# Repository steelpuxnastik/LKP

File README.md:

# LKP

レンくんピアノ (Len-kun Piano)

Capacitive touch slider controller for rhythm games.

# Contents

## pcb/LKP-Core

Microcontroller board for use with LKP electrode boards. Supports up to 32 channel of self capacitance input. Includes a WS281x LED driver channel with protection resistor. Supports I2C or UART as communication methods.

For sample firmware for use with LKP-Core, see [LKP-FW](https://github.com/Project-Alpaca/LKP-FW).

Requires KiCad version 5.99 (nightly) (supports `kicad_pcb format >= 20210816`).

### Pin mapping

I/O port:

| \#  | Description |
| --- | ----------- |
|  1  | GND |
|  2  | INT |
|  3  | SCL/RX |
|  4  | SDA/TX |
|  5  | GND |
|  6  | +5V |

WS281x LED connector:

| \#  | Description |
| --- | ----------- |
|  1  | GND |
|  2  | LED |

SWD connector:

| \#  | Description |
| --- | ----------- |
|  1  | VTARG |
|  2  | GND |
|  3  | RESET |
|  4  | SWCLK |
|  5  | SWDIO |

## pcb/LKP-Diva-Electrode-Tile

Electrode board for Project DIVA Future Tone slider controller. Works as a 2-tile setup. Both tiles use the same design, with right tile being a 180 degree rotated version of the left tile.

Requires KiCad version 5.99 (nightly) (supports `kicad_pcb format >= 20210228`) for hatched fills.

# BOM

## LKP-Core

- **C1, C4, C6, C10**: Generic 1uF 0603 X5R ceramic capacitor. (I used `CC0603KRX5R8BB105`)
- **C2, C3, C5, C8, C11**: Generic 100nF 0603 ceramic capacitor. (I used `CL10B104KA8NNNC`)
- **C7**: `GRM2195C1H103JA01D`.
- **C9**: `GRM21B5C2J222FWAAL`.
- **C12**: Generic 10uF EIA-3216-18 tantalum capacitor.
- **D1**: Generic SOD-123 Schottky diode (`MBR0520L`).
- **D2**: Generic 0805 LED (yellow color).
- **FB1**: Generic 1206 ferrite bead (330ohm@100MHz).
- **J1, J2**: Straight female .1" header 2x9.
- **J3**: JST XH 2 positions.
- **J4**: Straight male .1" header 1x6.
- **J5**: Straight male .1" header 1x5.
- **J6**: **Angled** male .1" header 1x2 or JST XH 2 positions
- **R1**: Generic 1kohm 5% 0603 resistor.
- **R2**: Generic 470ohm 5% 0603 resistor.
- **R3, R4**: Generic 560ohm 5% 0603 resistor.
- **RN\***: Generic 560ohm 5% 0402x4 convex resistor array (I used `4D02WGJ0561TCE`).
- **U1**: `CY8C4246AZI-M445` (or `CY8C4247AZI-M485`, Needs minor firmware modifications).

## LKP-Diva-Electrode-Tile

- **J1**: Straight male .1" SMD header 2x9 (**without** bumps at the bottom).
  - This can be hard to find. For small scale DIY manufacturing try searching "pin header double smd" on aliexpress.

# Powering

By default LKP expects 5V power. Using lower supply voltage down to 1.8V is possible by modifying the power specs in LKP-FW and adding a level shifter module to the WS281x driver pin (labeled as LED on board). Reference voltage for I/O can be approximated by tapping into the VTARG pin on the SWD port.

# Known issues / Erratas

- (LKP-Core v1.0) The reverse voltage protection diode (D1) does not protect C12. Proceed with caution when connecting the power to make sure the polarity is correct.
- (LKP-Core v1.1) When used with LKP-Assy, connector J4, J5 and J6 may collide with the bottom of LKP-Assy. A workaround would be soldering all the specified connectors on the back side of the PCB instead. Also, when using LKP-IF-Qwiic, J4 and J5 must be soldered on the back side.
- (LKP-Core v1.2b) Changes of some parts that I have and I want to use: J1, J2 to JST XH, J4 from 4 to 6 pin, C9 to 0805 size, FB1 to 1206 size and changes in silkscreen. 

[qwiic]: https://www.sparkfun.com/qwiic
[stemmaqt]: https://learn.adafruit.com/introducing-adafruit-stemma-qt/what-is-stemma-qt

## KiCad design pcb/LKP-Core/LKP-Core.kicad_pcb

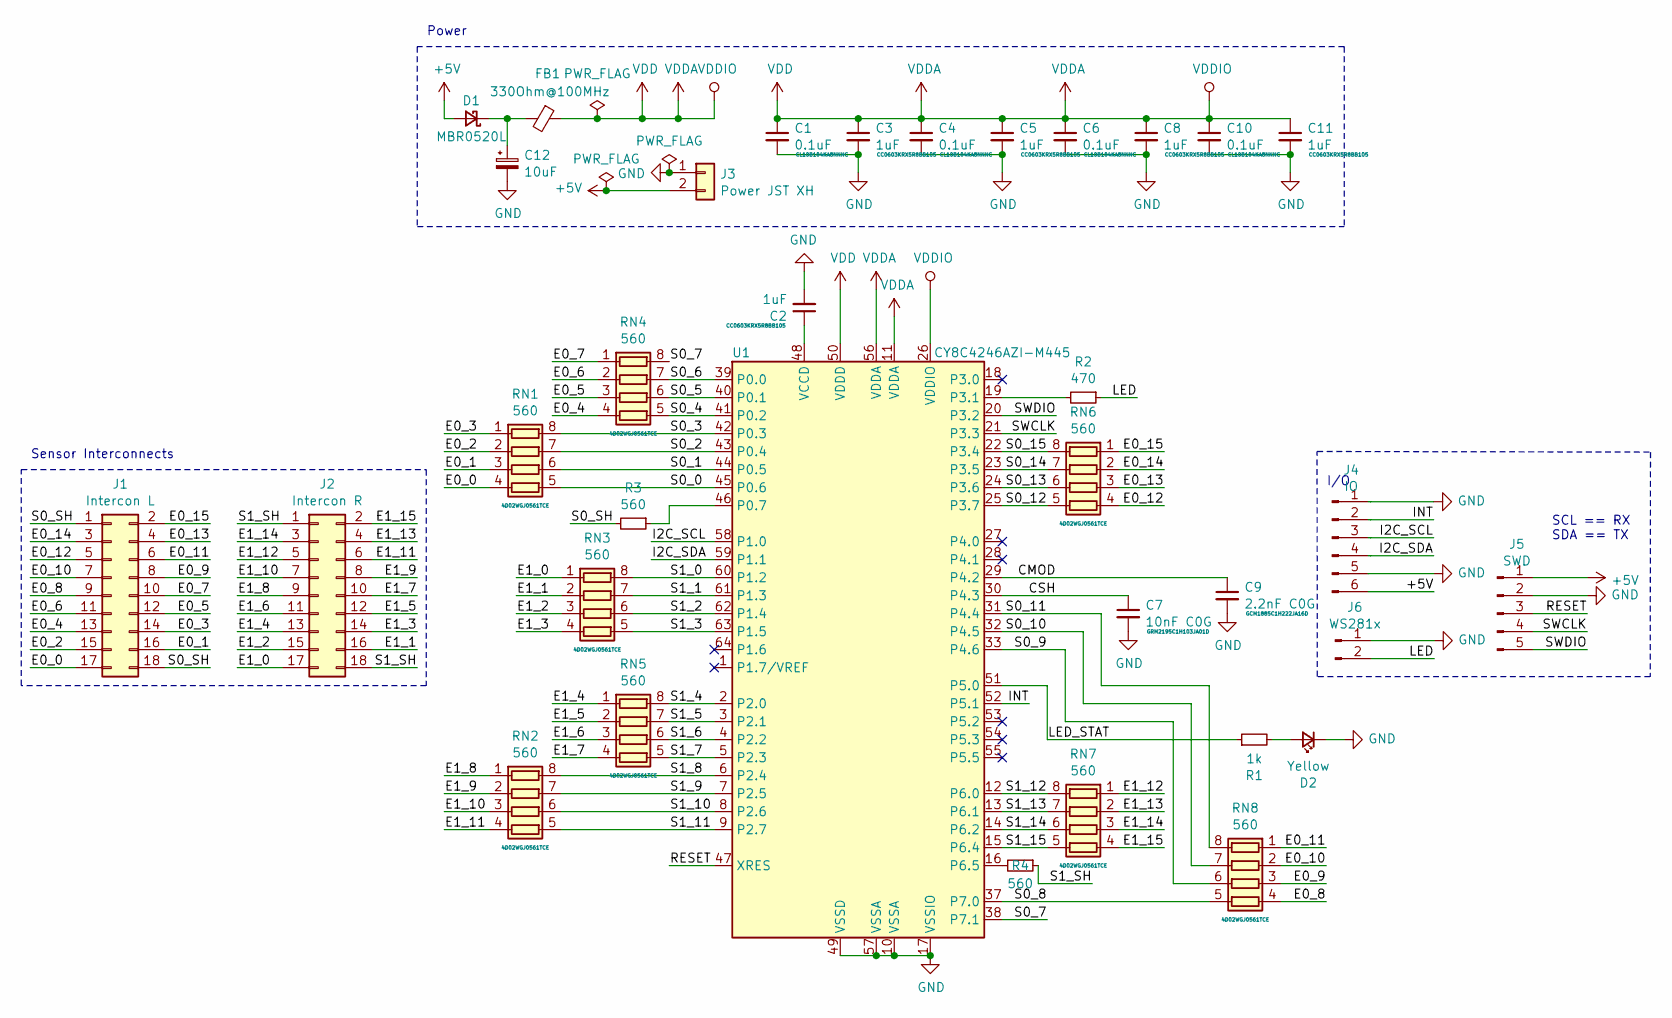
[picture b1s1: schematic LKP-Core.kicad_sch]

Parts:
C1, C4, C6, C10: 0.1uF; C_0603_1608Metric; Part Number CL10B104KA8NNNC
C2, C3, C5, C8, C11: 1uF; C_0603_1608Metric; Part Number CC0603KRX5R8BB105
C7: 10nF C0G; C_0805_2012Metric; Part Number GRM2195C1H103JA01D
C9: 2.2nF C0G; C_0805_2012Metric; Part Number GCM1885C1H222JA16D
C12: 10uF; CP_EIA-3216-18_Kemet-A
D1: MBR0520L; D_SOD-123; Part Number MBR0520L
D2: Yellow; LED_0805_2012Metric_Castellated
FB1: 330Ohm@100MHz; L_1206_3216Metric
J1: Intercon L; PinSocket_2x09_P2.54mm_Vertical
J2: Intercon R; PinSocket_2x09_P2.54mm_Vertical
J3: Power JST XH; JST_XH_B2B-XH-A_1x02_P2.50mm_Vertical
J4: IO; PinHeader_1x06_P2.54mm_Vertical
J5: SWD; PinHeader_1x05_P2.54mm_Vertical
J6: WS281x; JST_XH_B2B-XH-A_1x02_P2.50mm_Vertical
R1: 1k; R_0603_1608Metric
R2: 470; R_0603_1608Metric
R3, R4: 560; R_0603_1608Metric
RN1, RN2, RN3, RN4, RN5, RN6, RN7, RN8: 560; R_Array_Convex_4x0402; Part Number 4D02WGJ0561TCE
U1: CY8C4246AZI-M445; TQFP-64_10x10mm_P0.5mm; Part Number CY8C4246AZI-M445

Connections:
+5V: D1.2 (A), J3.2, J4.6, J5.1
/CMOD: C9.1, U1.29 (P4.2)
/CSH: C7.1, U1.30 (P4.3)
/E0_0: J1.17, RN1.4 (R4.1)
/E0_1: J1.16, RN1.3 (R3.1)
/E0_2: J1.15, RN1.2 (R2.1)
/E0_3: J1.14, RN1.1 (R1.1)
/E0_4: J1.13, RN4.4 (R4.1)
/E0_5: J1.12, RN4.3 (R3.1)
/E0_6: J1.11, RN4.2 (R2.1)
/E0_7: J1.10, RN4.1 (R1.1)
/E0_8: J1.9, RN8.4 (R4.1)
/E0_9: J1.8, RN8.3 (R3.1)
/E0_10: J1.7, RN8.2 (R2.1)
/E0_11: J1.6, RN8.1 (R1.1)
/E0_12: J1.5, RN6.4 (R4.1)
/E0_13: J1.4, RN6.3 (R3.1)
/E0_14: J1.3, RN6.2 (R2.1)
/E0_15: J1.2, RN6.1 (R1.1)
/E1_0: J2.17, RN3.1 (R1.1)
/E1_1: J2.16, RN3.2 (R2.1)
/E1_2: J2.15, RN3.3 (R3.1)
/E1_3: J2.14, RN3.4 (R4.1)
/E1_4: J2.13, RN5.1 (R1.1)
/E1_5: J2.12, RN5.2 (R2.1)
/E1_6: J2.11, RN5.3 (R3.1)
/E1_7: J2.10, RN5.4 (R4.1)
/E1_8: J2.9, RN2.1 (R1.1)
/E1_9: J2.8, RN2.2 (R2.1)
/E1_10: J2.7, RN2.3 (R3.1)
/E1_11: J2.6, RN2.4 (R4.1)
/E1_12: J2.5, RN7.1 (R1.1)
/E1_13: J2.4, RN7.2 (R2.1)
/E1_14: J2.3, RN7.3 (R3.1)
/E1_15: J2.2, RN7.4 (R4.1)
/I2C_SCL: J4.3, U1.58 (P1.0)
/I2C_SDA: J4.4, U1.59 (P1.1)
/INT: J4.2, U1.52 (P5.1)
/LED: J6.2, R2.1
/LED_STAT: R1.1, U1.51 (P5.0)
/RESET: J5.3, U1.47 (XRES)
/S0_0: RN1.5 (R4.2), U1.45 (P0.6)
/S0_1: RN1.6 (R3.2), U1.44 (P0.5)
/S0_2: RN1.7 (R2.2), U1.43 (P0.4)
/S0_3: RN1.8 (R1.2), U1.42 (P0.3)
/S0_4: RN4.5 (R4.2), U1.41 (P0.2)
/S0_5: RN4.6 (R3.2), U1.40 (P0.1)
/S0_6: RN4.7 (R2.2), U1.39 (P0.0)
/S0_7: RN4.8 (R1.2), U1.38 (P7.1)
/S0_8: RN8.5 (R4.2), U1.37 (P7.0)
/S0_9: RN8.6 (R3.2), U1.33 (P4.6)
/S0_10: RN8.7 (R2.2), U1.32 (P4.5)
/S0_11: RN8.8 (R1.2), U1.31 (P4.4)
/S0_12: RN6.5 (R4.2), U1.25 (P3.7)
/S0_13: RN6.6 (R3.2), U1.24 (P3.6)
/S0_14: RN6.7 (R2.2), U1.23 (P3.5)
/S0_15: RN6.8 (R1.2), U1.22 (P3.4)
/S0_SH: J1.1, J1.18, R3.2
/S1_0: RN3.8 (R1.2), U1.60 (P1.2)
/S1_1: RN3.7 (R2.2), U1.61 (P1.3)
/S1_2: RN3.6 (R3.2), U1.62 (P1.4)
/S1_3: RN3.5 (R4.2), U1.63 (P1.5)
/S1_4: RN5.8 (R1.2), U1.2 (P2.0)
/S1_5: RN5.7 (R2.2), U1.3 (P2.1)
/S1_6: RN5.6 (R3.2), U1.4 (P2.2)
/S1_7: RN5.5 (R4.2), U1.5 (P2.3)
/S1_8: RN2.8 (R1.2), U1.6 (P2.4)
/S1_9: RN2.7 (R2.2), U1.7 (P2.5)
/S1_10: RN2.6 (R3.2), U1.8 (P2.6)
/S1_11: RN2.5 (R4.2), U1.9 (P2.7)
/S1_12: RN7.8 (R1.2), U1.12 (P6.0)
/S1_13: RN7.7 (R2.2), U1.13 (P6.1)
/S1_14: RN7.6 (R3.2), U1.14 (P6.2)
/S1_15: RN7.5 (R4.2), U1.15 (P6.4)
/S1_SH: J2.1, J2.18, R4.1
/SWCLK: J5.4, U1.21 (P3.3)
/SWDIO: J5.5, U1.20 (P3.2)
GND: C1.2, C2.2, C3.2, C4.2, C5.2, C6.2, C7.2, C8.2, C9.2, C10.2, C11.2, C12.2, D2.1 (K), J3.1, J4.1, J4.5, J5.2, J6.1, U1.10 (VSSA), U1.17 (VSSIO), U1.49 (VSSD), U1.57 (VSSA)
unnamed: C2.1, U1.48 (VCCD)
unnamed: C12.1, D1.1 (K), FB1.2
unnamed: D2.2 (A), R1.2
unnamed: R2.2, U1.19 (P3.1)
unnamed: R3.1, U1.46 (P0.7)
unnamed: R4.2, U1.16 (P6.5)
VDD: C1.1, C3.1, C4.1, C5.1, C6.1, C8.1, C10.1, C11.1, FB1.1, U1.11 (VDDA), U1.26 (VDDIO), U1.50 (VDDD), U1.56 (VDDA)

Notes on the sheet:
Sensor Interconnects
Power
I/O
SCL == RX SDA == TX

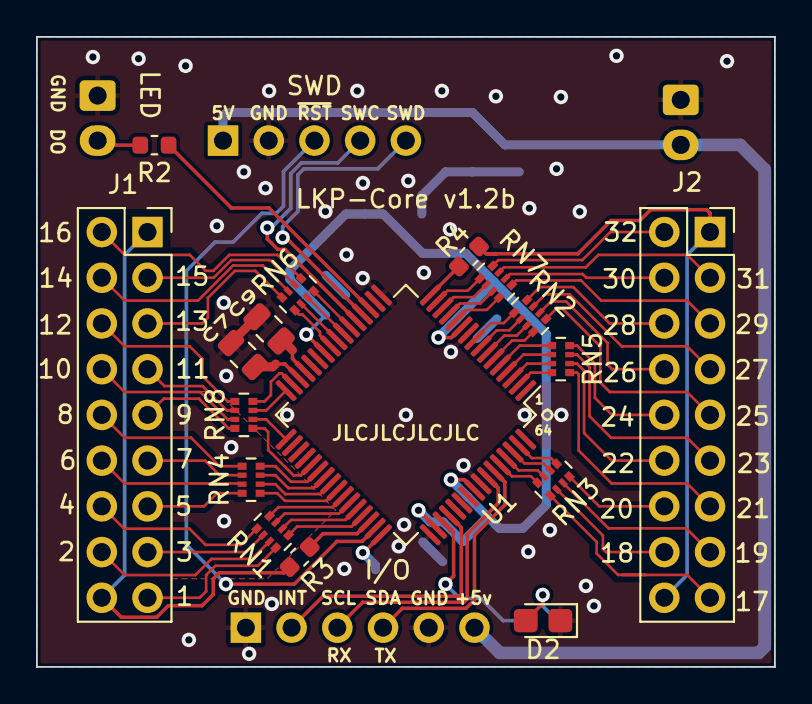
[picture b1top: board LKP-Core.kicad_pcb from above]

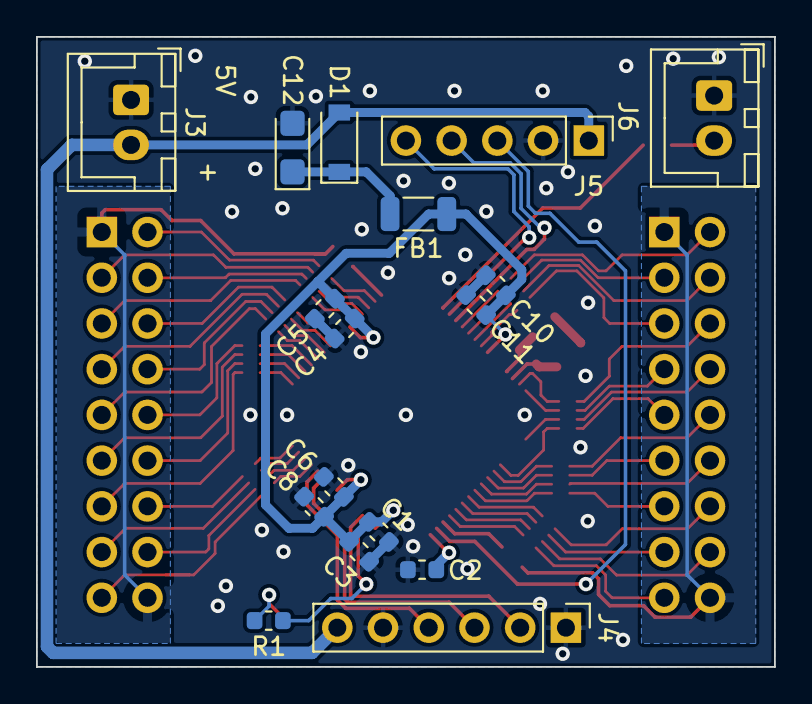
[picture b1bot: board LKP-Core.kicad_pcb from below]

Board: 2 copper layers, 41.0 x 35.0 mm, 34 parts (17 on the bottom side), 85 nets.

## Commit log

2021-08-30 As long as I did it long time ago
    Update with parts I have and I want to use to 1.2b, maybe will use it later
